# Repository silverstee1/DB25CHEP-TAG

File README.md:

# DB25CHEP-TAG
Cheap DB25 Parallel Port JTAG Programmer for IDE-EXI, USB Gecko and other XC95XX CPLD projects

Used on Xilinx Webpack ISE software suite to program the CPLD, I use version 13.3 in windows XP but it should work with any version that still supports Parallel cable 3

When using with Xilinx Impact under cable options choose Parallel cable 3

USB-C is only to provide power to the 3.3V regulator for the programmer/CPLD, the R3 and R4 5.1kOhm Resistors can be left out if you'll only be using a USB-C to A cable, they're only necessary with a C to C cable.

A nice 6pin Clip makes it easier to program most CPLDs that have 2.54mm pin JTAG headers on the pcb boards

I use this 6P clip https://www.aliexpress.us/item/3256805030490716.html 

# CHEP-TAG BOM

When Ordering/uploading the PCB gerbers to ex. JLCPCB I'd recommend to use 1.6mm thickness. The rest of the options can be default.

**U1:** <ins>AMS1117-3.3 SOT-223</ins>

DigiKey Part#: 5399-AMS1117-3.3SOT-223CT-ND

LCSC Part#: C426566

**C1, C2:** <ins>1206 10uF Tantalum Capacitors, + on PCB indicates the Stripe anode side of the cap</ins>

Digikey Part#: 718-TMCMA1C106KTRFCT-ND

LCSC Part#: C4988312

**D1:** <ins>1206 Blue 5ma LED, Led Green side Cathode orientation Marked with a Dot on pcb.</ins>

Digikey Part#: 2007-BL-HB333Q-AV-TRBCT-ND

LCSC Part#: C434440

Aliexpress Link: 1206 Blue https://www.aliexpress.us/item/3256805993208379.html

**R1:** <ins>4.7Kohm 1206 Resistor</ins>

Digikey Part#: 311-4.70KFRCT-ND

LCSC Part#: C137262

**R2:** <ins>10Rohm 1206 Resistor</ins>

Digikey Part#: 311-10.0FRCT-ND

LCSC Part#: C108080

**R3, R4:** <ins>5.1Kohm 0402 Resistors, (only necessary if you want to use USB-C to C cables can be unpopulated if using USB-C to A)</ins>

Digikey Part#: 311-5.1KJRCT-ND

LCSC Part#: C105873

**J1:** <ins>DB25 Male Right Angle Connector</ins>

Digikey Part#: A32100-ND

LCSC Part#: C305948

A cheap option is this 25P Male from Aliexpress https://www.aliexpress.us/item/3256805300852948.html?

remove the screw posts, and solder the front metal faceplate through the post holes filling the holes with lots of solder to the metal rear threads on the back to keep it in place, use plenty of Flux to help the solder stick to the metal.

**J2:** <ins>2.54mm 01x02 Male Pinheader (can be unpopulated, used as external +5V supply input to board instead of USB-C)</ins>

Can be found on Amazon, Ebay, Aliexpress etc. in any length just snip off however much you need.

Example Aliexpress Link https://www.aliexpress.us/item/3256807383526945.html

**J3:** <ins>2.54mm 01x06 Male Pinheader (can use either vertical or right angle 2.54mm header depending on preference)</ins>

Can be found on Amazon, Ebay, Aliexpress etc. in any length just snip off however much you need. 

Example Aliexpress link https://www.aliexpress.us/item/3256807383526945.html

**J5:** <ins>USB-C Female Connector</ins>

Digikey Part#: 52-USB-CB16HTBTRCT-ND

LCSC Part#: C165948

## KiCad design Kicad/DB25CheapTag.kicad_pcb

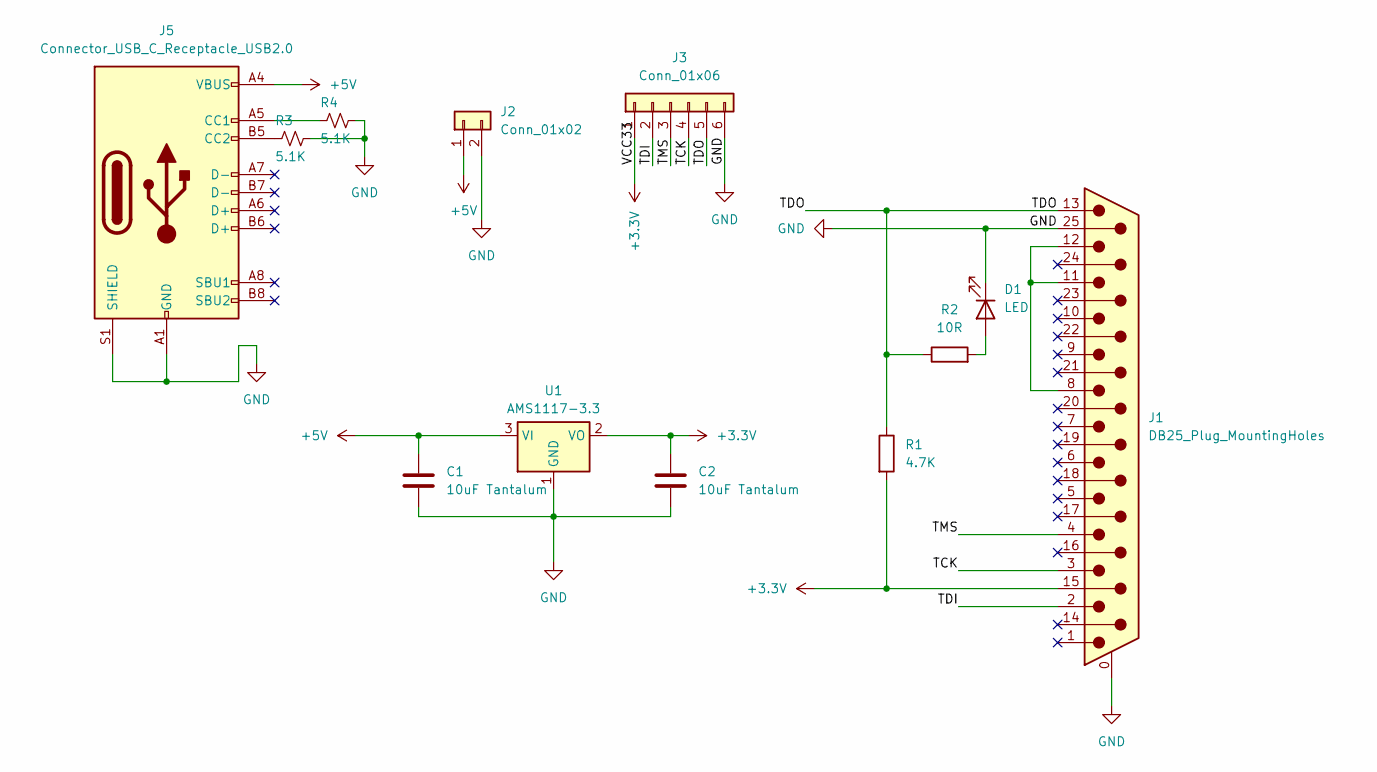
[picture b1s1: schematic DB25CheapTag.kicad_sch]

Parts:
C1, C2: 10uF Tantalum; C_1206_3216Metric_Pad1.33x1.80mm_HandSolder
D1: LED; LED_1206_3216Metric_Pad1.42x1.75mm_HandSolder
J1: DB25_Plug_MountingHoles; DSUB-25_Male_Horizontal_P2.77x2.84mm_EdgePinOffset7.70mm_Ho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
J2: Conn_01x02; PinHeader_1x02_P2.54mm_Vertical
J3: Conn_01x06; PinHeader_1x06_P2.54mm_Vertical
J5: Connector_USB_C_Receptacle_USB2.0; TYPE-C-31-M-12
R1: 4.7K; R_1206_3216Metric_Pad1.30x1.75mm_HandSolder
R2: 10R; R_1206_3216Metric_Pad1.30x1.75mm_HandSolder
R3, R4: 5.1K; R_0402_1005Metric_Pad0.72x0.64mm_HandSolder
U1: AMS1117-3.3; SOT-223-3_TabPin2

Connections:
+3.3V: C2.1, J1.15, J3.1, R1.2, U1.2 (VO)
+5V: C1.1, J2.1, J5.A4 (VBUS), J5.A9 (VBUS), J5.B4 (VBUS), J5.B9 (VBUS), U1.3 (VI)
/TCK: J1.3, J3.4
/TDI: J1.2, J3.2
/TDO: J1.13, J3.5, R1.1, R2.1
/TMS: J1.4, J3.3
GND: C1.2, C2.2, D1.1 (K), J1.0 (PAD), J1.25, J2.2, J3.6, J5.A1 (GND), J5.A12 (GND), J5.B1 (GND), J5.B12 (GND), J5.S1 (SHIELD), R3.1, R4.1, U1.1 (GND)
unnamed: D1.2 (A), R2.2
unnamed: J1.8, J1.11, J1.12
unnamed: J5.A5 (CC1), R4.2
unnamed: J5.B5 (CC2), R3.2

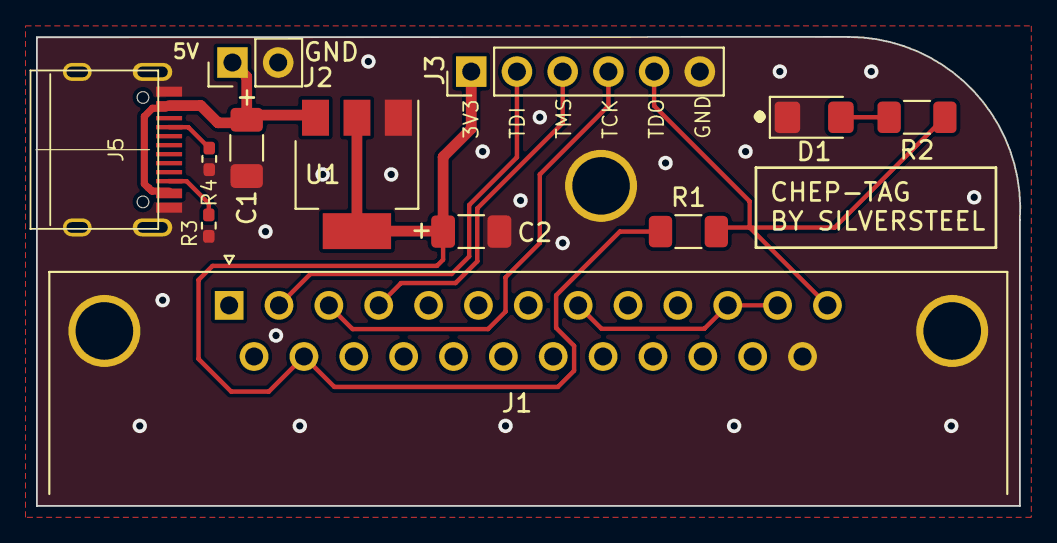
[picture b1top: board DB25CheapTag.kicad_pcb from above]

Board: 2 copper layers, 54.6 x 26.1 mm, 12 parts (0 on the bottom side), 11 nets.

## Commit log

2025-03-11 added pcb gerbers
2025-03-11 Add files via upload
    added Kicad Project
2025-03-11 Update README.md
    added pics
2025-03-11 Update README.md
    fix typos
2025-03-14 Add files via upload
    example order
